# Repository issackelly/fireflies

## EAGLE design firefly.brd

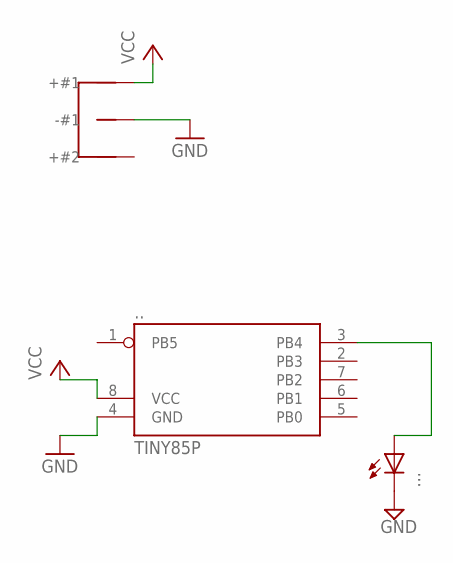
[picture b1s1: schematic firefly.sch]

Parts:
.: STRAP-BC-2003
..: TINY85P; DIL08
...: LED5MM

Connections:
GND: ..-#1, ..-#2 (-#1), ...4 (GND), ....K (C)
unnamed: ...3 (PB4), ....A
VCC: ..+#1, ...8 (VCC)

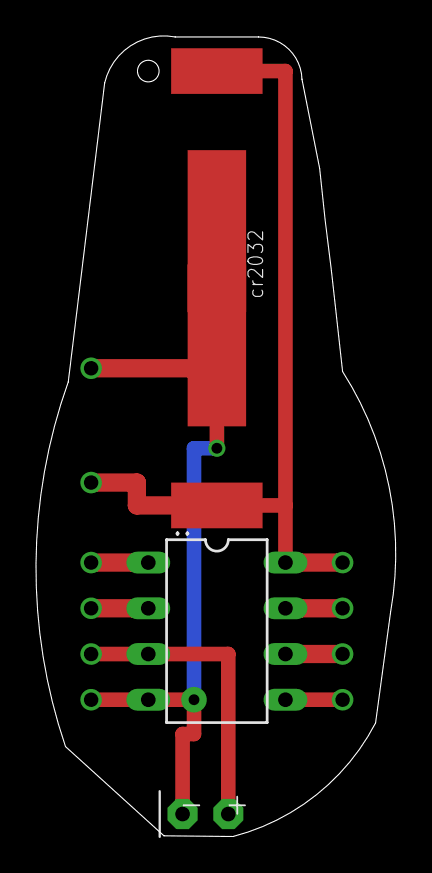
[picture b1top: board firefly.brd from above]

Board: 2 copper layers, 20.0 x 44.5 mm, 3 parts (0 on the bottom side), 3 nets.
